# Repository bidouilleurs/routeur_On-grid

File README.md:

# routeur_On-grid

Version du routeur DC modifié avec 1 diode pour connaitre le sens du transfert de puissance ( sens du courant ) 

-les entrées de la pince DC sont utilisées pour raccorder des pinces AC ( 30A, 1V) 

-la régulation se fait sur le courant inverse (injection) règlé avec le tolérance-négative 

-sur la page web il faut lire Le Courant AC dans intensité batterie 

-la fonction relais statique et thermostat sont inversé si la température du ballon descent en dessous d'une valeur, le relais s'enclenche 

-on pourra donc l'associer au relais Heures creuses pour maintenir la température si le soleil n'est pas au rendez-vous 

-Les informations MQTT restent identiques

Fichiers modifiés du routeur off-grid

source.ino

triac.cpp ( tient compte de la diode ) 

mesure.cpp et .h

regulation.cpp et .h

plus de simulation.cpp

le reste est identique

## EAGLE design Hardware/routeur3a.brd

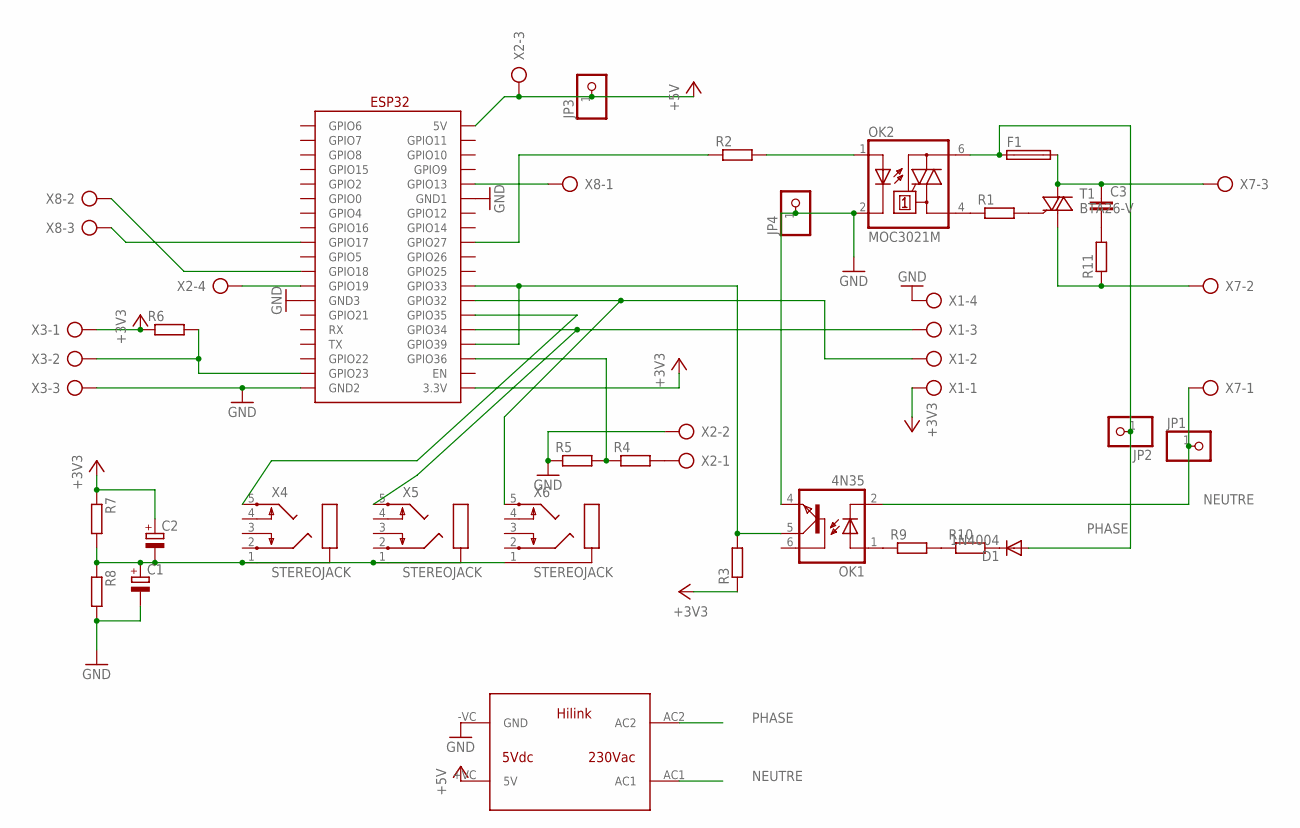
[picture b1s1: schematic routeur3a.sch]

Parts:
C1, C2: CPOL-EUE5-8.5; E5-8,5
C3: C-EU150-072X183; C150-072X183
D1: 1N4004; DO41-10
F1: 19560
JP1, JP2, JP3, JP4: PINHD-1X1; 1X01
OK1: 4N35; DIL06
OK2: MOC3021M; DIL06
R1, R9, R10: R-EU_0207/10; 0207/10
R2, R3, R4, R5, R6, R7, R8: R-EU_R1206; R1206
R11: R-EU_0817/22; P0817/22
T1: BTA26-V; TOP3S-1
U$1: WEMOSD1ESP32; WEMOS-D1-MINI
U$2: HILINK
X1, X2: AK500/4
X3, X7, X8: AK500/3
X4, X5, X6: STEREOJACK; STX3100

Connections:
+3V3: C2.+, R3.1, R6.1, R7.1, U$1.3V3 (3.3V), X1.1, X3.1
+5V: JP3.1, U$1.VCC (5V), U$2.+VC (5V), X2.3
GND: C1.-, JP4.1, OK1.4 (EMI), OK2.2 (C), R5.1, R8.2, U$1.GND (GND1), U$1.GND2, U$1.GND3, U$2.-VC (GND), X1.4, X2.2, X3.3
unnamed: OK2.4 (A1), R1.1
unnamed: OK2.1 (A), R2.2
unnamed: R4.2, X2.1
unnamed: R1.2, T1.G
unnamed: C3.1, F1.2, T1.A2, X7.3
unnamed: R11.1, T1.A1, X7.2
unnamed: OK1.1 (A), R9.1
unnamed: R9.2, R10.1
unnamed: U$1.TCK (GPIO13), X8.1
unnamed: D1.C, R10.2
unnamed: C1.+, C2.-, R7.2, R8.1, X4.1, X5.1, X6.1
unnamed: C3.2, R11.2
unnamed: U$1.35 (GPIO35), X4.5
NEUTRE: JP1.1, OK1.2 (C), U$2.AC1, X7.1
PHASE: D1.A, F1.1, JP2.1, OK2.6 (A2), U$2.AC2
PINCE: U$1.32 (GPIO32), X1.2, X6.5
PINCEREF: U$1.34 (GPIO34), X1.3, X5.5
PZEMRX: U$1.17 (GPIO17), X8.3
PZEMTX: U$1.18 (GPIO18), X8.2
RELAIS: U$1.19 (GPIO19), X2.4
TEMP: R6.2, U$1.23 (GPIO23), X3.2
TENSION: R4.1, R5.2, U$1.SVP (GPIO36)
TRIAC: R2.1, U$1.27 (GPIO27)
ZC: OK1.5 (COL), R3.2, U$1.33 (GPIO33), U$1.SUN (GPIO39)

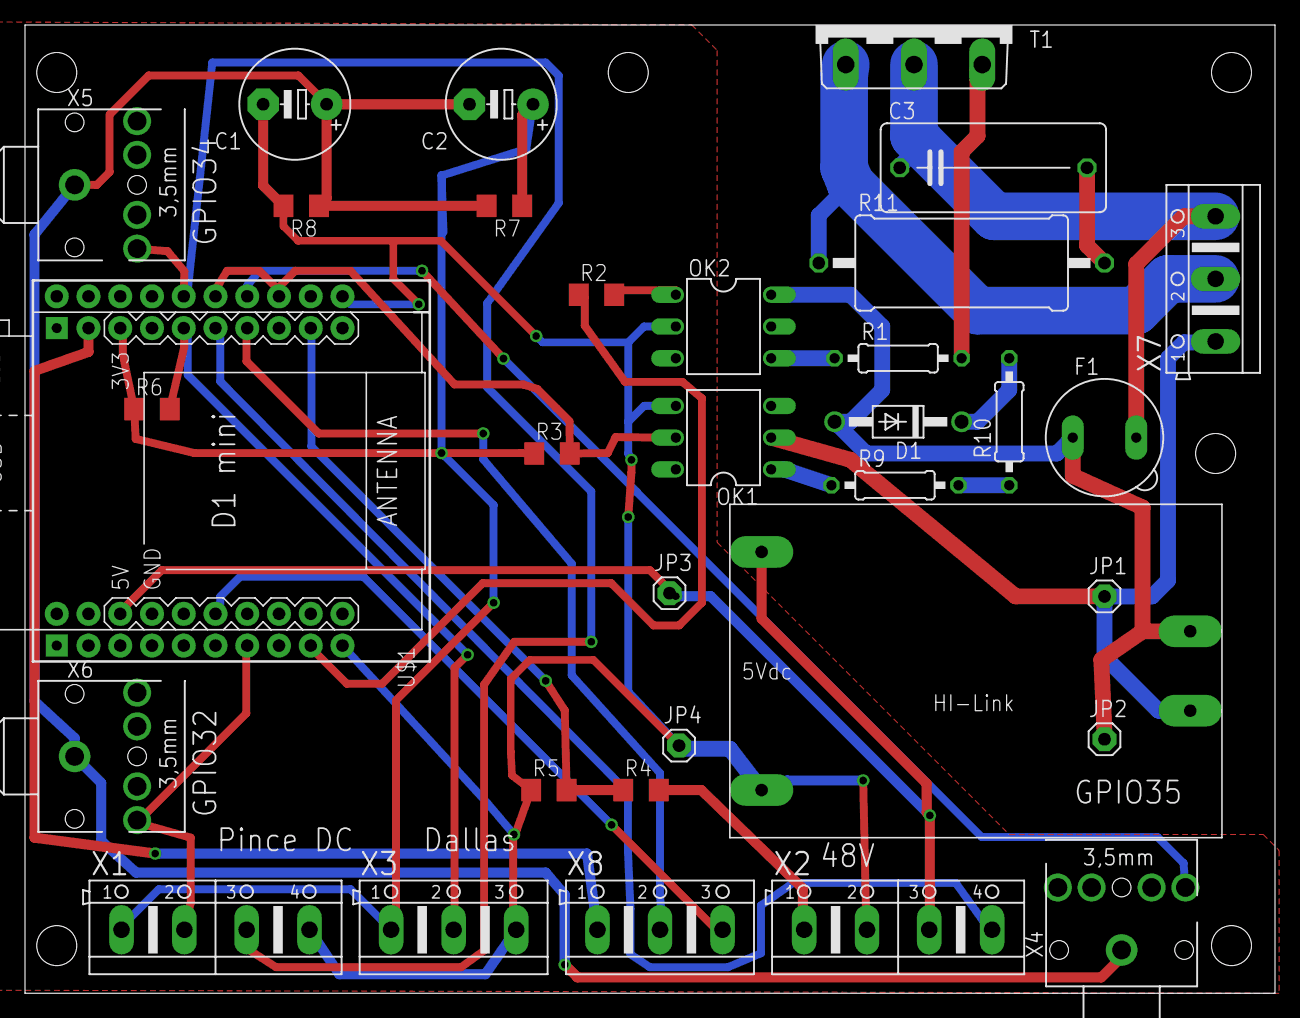
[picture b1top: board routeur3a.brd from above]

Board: 2 copper layers, 100.0 x 77.5 mm, 33 parts (0 on the bottom side), 27 nets.

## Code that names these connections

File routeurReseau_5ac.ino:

//**************************************************************/
// L'équipe de bidouilleurs discord reseautonome vous présente
// la réalisation d'un gradateur pour chauffe-eau en off grid
// gradateur synchronisé sur la production photovoltaique
// sans tirage sur les batteries pour utiliser le surplus dans
// un ballon d'eau chaude
//**************************************************************/

const char *version_soft = "Version 1.5 AC-DC avec 1 diode ZC"  ;

//**************************************************************/
// Initialisation
//**************************************************************/
#include "settings.h"
struct param routeur;
const int zeroc = 33;            // GPIO33  passage par zéro de la sinusoide
const int pinTriac = 27;         // GPIO27 triac
// analogique
const int pinPince = 32;         // GPIO32   pince effet hall
const int pinPinceAC = 32;         // GPIO32   pince effet hall
const int pinPinceACref = 39;    // GPIO39   ref tension pour pince AC 30A/1V
const int pinPinceRef = 34;      // GPIO34   pince effet hall ref 2.5V
const int pinPotentiometre = 35; // GPIO35   potentiomètre
const int pinTension = 36;       // GPIO36   capteur tension
const int pinTemp = 23;          // GPIO23  capteurTempérature
const int pinSortie2 = 13;       // pin13 pour  2eme "gradateur utilisée pour synchroniser le ZéroCrossing
const int pinRelais = 19;        // Pin19 pour sortie relais


bool marcheForcee = false;
short int marcheForceePercentage = 25;
short int sortieActive = 1;
unsigned long temporisation = 60;
float intensiteBatterie = 0;
float capteurTension = 0;
int puissanceGradateur = 0;
float temperatureEauChaude = 0;
float puissanceDeChauffe = 0;
float puissanceAC = 0;
float intensiteAC = 0;
bool etatRelaisStatique = false;
bool modeparametrage = false;

int resetEsp = 0;
int testwifi = 0;
int choixSortie = 0;
int paramchange = 0;
bool SAP = false;
bool MQTT = false;
bool serverOn = false;

/**********************************************/
/********** déclaration des librairiess *******/
/**********************************************/
#include "triac.h"

#ifdef WifiMqtt
#include "modemqtt.h"
#endif

#ifdef WifiServer
#include "modeserveur.h"
#endif

#ifdef EEprom
#include "prgEEprom.h"
#endif

#ifdef EcranOled
#include "afficheur.h"
#endif

#ifdef Bluetooth
#include "modeBT.h"
#endif

//#define simulation // utiliser pour faire les essais sans les accessoires
#ifdef simulation
#include "simulation.h"
#endif

#include "mesure.h"
#include "regulation.h"

/***************************************/
/******** Programme principal   ********/
/***************************************/
void setup()
{

  Serial.begin(115200);

  pinMode(pinTriac, OUTPUT);  digitalWrite(pinTriac, LOW); // mise à zéro du triac au démarrage
  pinMode(pinSortie2, OUTPUT);  digitalWrite(pinSortie2, LOW); // mise à zéro du triac de la sortie 2
  pinMode(pinRelais, OUTPUT);  digitalWrite(pinRelais, HIGH); // mise à zéro du relais statique
  pinMode(zeroc,INPUT);
  pinMode(pinTemp, INPUT);
  pinMode(pinTension, INPUT);
  pinMode(pinPotentiometre, INPUT);
  pinMode(pinPince, INPUT);
  pinMode(pinPinceRef, INPUT);
  pinMode(pinPinceACref, INPUT);
  Serial.println();
  Serial.println(F("definition ok "));
  Serial.println(version_soft);
  Serial.println();

#ifdef EcranOled
  RAAfficheur.setup();
#endif


#ifdef EEprom
  RAPrgEEprom.setup();
#endif

  delay(500);
  marcheForcee = false; // mode forcé retirer au démarrage
  marcheForceePercentage = false;
  temporisation = 0;
  
#ifdef WifiMqtt
  RAMQTT.setup();
#endif

#ifdef WifiServer
  RAServer.setup(); // activation de la page Web de l'esp
#endif

#ifdef Bluetooth // bluetooth non autorise avec serveur web ou MQTT
  RABluetooth.setup();
#endif

#ifdef EcranOled
  RAAfficheur.setup();
#endif

#ifdef MesureTemperature
  RAMesure.setup();
#endif

#ifdef Pzem04t
  Serial2.begin(9600, SERIAL_8N1, RXD2, TXD2); // redefinition des broches du serial2
#endif

#ifdef parametrage
  modeparametrage = true;
#endif

#ifdef relaisPWM
  ledcAttachPin(pinRelais, 0); // broche 18, canal 0.
  ledcSetup(0, 5000, 10); // canal = 0, frequence = 5000 Hz, resolution = 10 bits 1024points
#endif


  delay(500);
  RATriac.watchdog(0);       // initialise le watchdog
  RATriac.start_interrupt(); // demarre l'interruption de zerocrossing et du timer pour la gestion du triac

}

int iloop = 0; // pour le parametrage par niveau


void loop()
{
  RATriac.watchdog(1);                  //chien de garde à 4secondes dans timer0
    RAMesure.mesureTemperature(); // mesure la temperature sur le ds18b20
    RAMesure.mesure_puissance();  // mesure la puissance sur le pzem004t
    intensiteBatterie=RAMesure.mesurePinceAC(pinPinceAC,0.350,true);

    RARegulation.pilotage();
     if (!marcheForcee) 
        {
          puissanceGradateur = RARegulation.regulGrad(-routeur.toleranceNegative,5,5,5);
         }
  
  // affichage traceur serie
 float c = puissanceGradateur;
  Serial.print(" ");
  Serial.print(c / 100);
   Serial.print(',');
  Serial.print(intensiteAC);
   Serial.print(',');
  Serial.println(-0.2);
 /* Serial.print(',');
  Serial.print(routeur.seuilDemarrageBatterie / 5);
  Serial.print(',');
  Serial.print(capteurTension / 5);
  Serial.print(',');
  Serial.println(-routeur.toleranceNegative);
*/
//  Serial.print(',');
//  Serial.print(intensiteAC) );
//  Serial.print(',');
//  Serial.println(puissanceAC/100);

//RAMesure.mesurePinceAC(pinPince,0.321,false);
//puissanceGradateur=300;

#ifdef relaisPWM
  ledcWrite(0, long(puissanceGradateur*1024/1000));  //  canal = 0, rapport cyclique = 
#endif

#ifdef EcranOled
 RAAfficheur.affichage_oled(); // affichage de lcd
#endif

#ifdef WifiMqtt
  RAMQTT.loop();
#endif

#ifdef WifiServer
  RAServer.loop();
  RAServer.coupure_reseau();
#endif


#ifdef EEprom
  
  if (resetEsp == 1)
  {
    RATriac.stop_interrupt();
    RAPrgEEprom.close_param(); 
    delay(5000);
  }
#endif

  if (resetEsp == 1)
  {
    Serial.println("Restart !");
    ESP.restart(); // redemarrage
  }
}
